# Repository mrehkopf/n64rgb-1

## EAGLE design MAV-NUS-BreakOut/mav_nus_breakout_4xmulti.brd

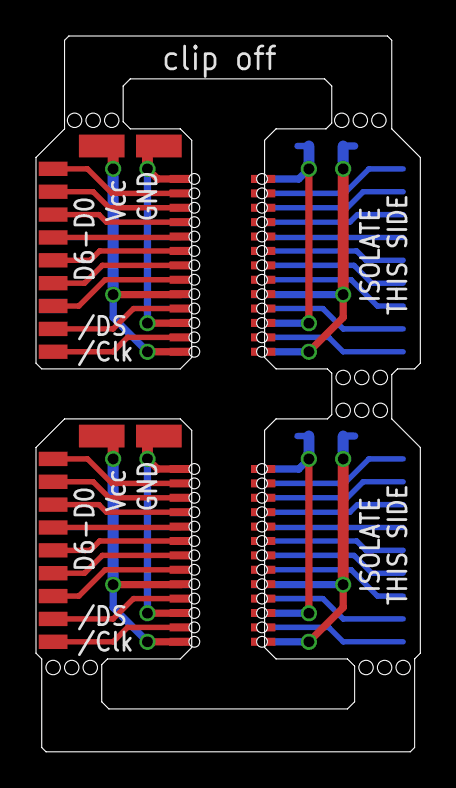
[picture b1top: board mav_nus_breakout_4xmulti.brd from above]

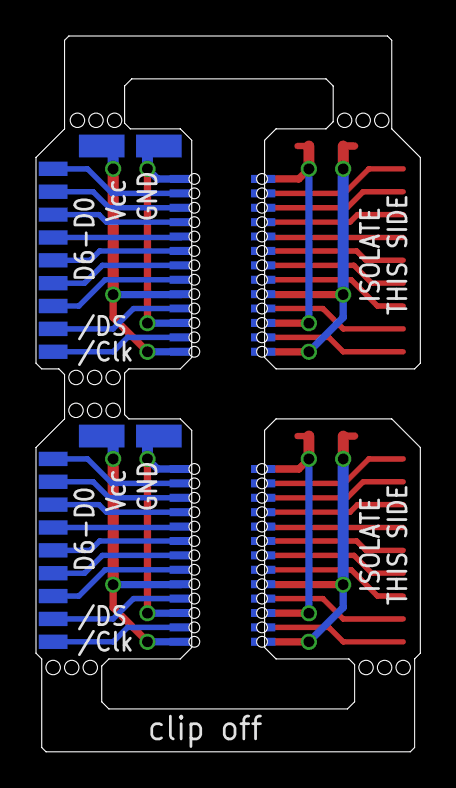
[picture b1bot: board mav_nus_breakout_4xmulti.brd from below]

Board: 2 copper layers, 21.4 x 39.8 mm, 148 parts (74 on the bottom side), 44 nets.

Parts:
PAD1, PAD2, PAD3, PAD4, PAD5, PAD6, PAD7, PAD8: SMD1,27-2,54
U$1, U$2, U$3, U$4, U$5, U$6, U$7, U$8, U$9, U$10, U$11, U$12, U$13, U$23, U$24, U$25, U$26, U$27, U$28, U$29, U$30, U$31, U$32, U$33, U$34, U$35, U$36, U$37, U$38, U$39, U$40, U$47, U$51, U$52, U$53, U$54, U$55, U$56, U$57, U$58, U$59, U$60, U$61, U$62, U$63, U$64, U$65, U$66, U$67, U$68, U$69, U$70, U$71, U$72, U$73, U$74, U$75, U$82, U$86, U$87, U$88, U$89, U$90, U$91, U$92, U$93, U$94, U$95, U$96, U$97, U$98, U$99, U$100, U$101, U$102, U$103, U$104, U$105, U$106, U$107, U$108, U$109, U$110, U$117, U$121, U$122, U$123, U$124, U$125, U$126, U$127, U$128, U$129, U$130, U$131, U$132, U$133, U$134, U$135, U$136, U$137, U$138, U$139, U$140: SMD0,45; SMD0,45-1,35
U$14, U$15, U$16, U$17, U$18, U$19, U$20, U$21, U$22, U$41, U$42, U$43, U$44, U$45, U$46, U$48, U$49, U$50, U$76, U$77, U$78, U$79, U$80, U$81, U$83, U$84, U$85, U$111, U$112, U$113, U$114, U$115, U$116, U$118, U$119, U$120: SMD1; SMD0,8-1,6

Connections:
unnamed: U$1.P$1, U$14.P$1
unnamed: U$2.P$1, U$15.P$1
unnamed: U$3.P$1, U$16.P$1
unnamed: U$4.P$1, U$17.P$1
unnamed: U$5.P$1, U$18.P$1
unnamed: U$6.P$1, U$19.P$1
unnamed: U$7.P$1, U$20.P$1
unnamed: U$8.P$1, U$21.P$1
unnamed: U$9.P$1, U$22.P$1
unnamed: PAD1.1, U$10.P$1, U$11.P$1
unnamed: PAD2.1, U$12.P$1, U$13.P$1
unnamed: U$36.P$1, U$41.P$1
unnamed: U$42.P$1, U$47.P$1
unnamed: U$43.P$1, U$51.P$1
unnamed: U$44.P$1, U$52.P$1
unnamed: U$45.P$1, U$53.P$1
unnamed: U$46.P$1, U$54.P$1
unnamed: U$48.P$1, U$55.P$1
unnamed: U$49.P$1, U$56.P$1
unnamed: U$50.P$1, U$57.P$1
unnamed: PAD3.1, U$37.P$1, U$38.P$1
unnamed: PAD4.1, U$39.P$1, U$40.P$1
unnamed: U$71.P$1, U$76.P$1
unnamed: U$77.P$1, U$82.P$1
unnamed: U$78.P$1, U$86.P$1
unnamed: U$79.P$1, U$87.P$1
unnamed: U$80.P$1, U$88.P$1
unnamed: U$81.P$1, U$89.P$1
unnamed: U$83.P$1, U$90.P$1
unnamed: U$84.P$1, U$91.P$1
unnamed: U$85.P$1, U$92.P$1
unnamed: PAD5.1, U$72.P$1, U$73.P$1
unnamed: PAD6.1, U$74.P$1, U$75.P$1
unnamed: U$106.P$1, U$111.P$1
unnamed: U$112.P$1, U$117.P$1
unnamed: U$113.P$1, U$121.P$1
unnamed: U$114.P$1, U$122.P$1
unnamed: U$115.P$1, U$123.P$1
unnamed: U$116.P$1, U$124.P$1
unnamed: U$118.P$1, U$125.P$1
unnamed: U$119.P$1, U$126.P$1
unnamed: U$120.P$1, U$127.P$1
unnamed: PAD7.1, U$107.P$1, U$108.P$1
unnamed: PAD8.1, U$109.P$1, U$110.P$1

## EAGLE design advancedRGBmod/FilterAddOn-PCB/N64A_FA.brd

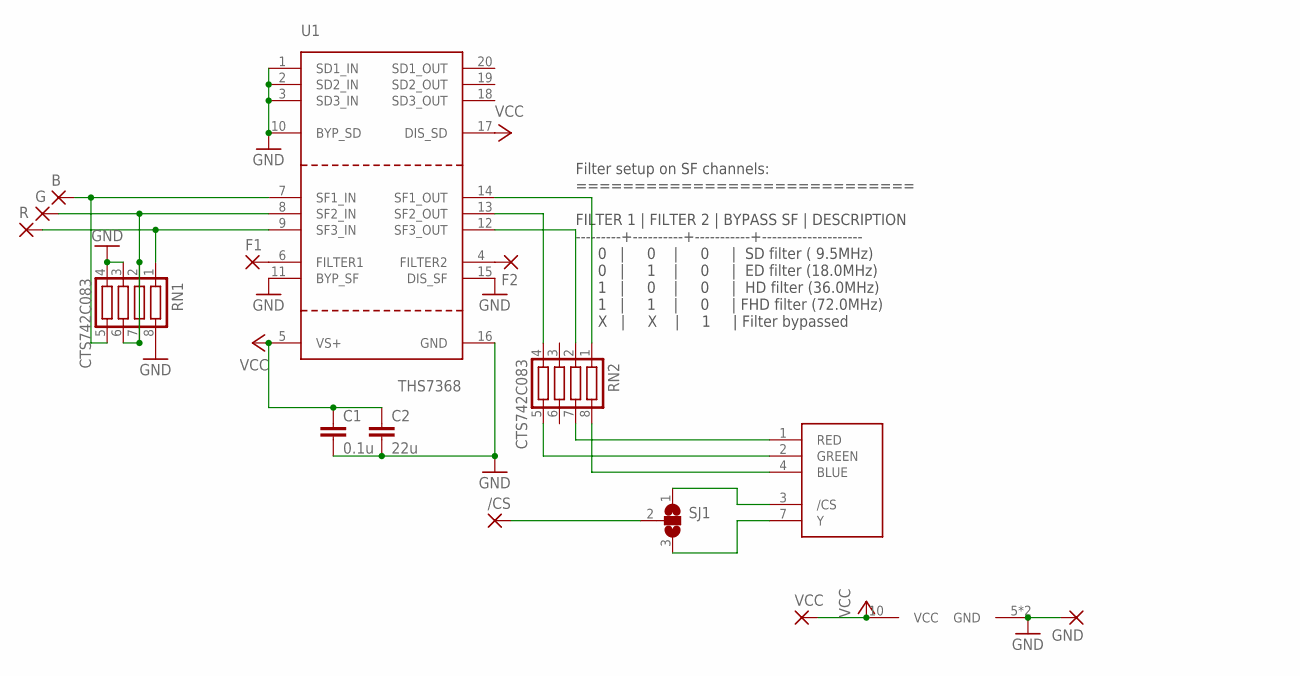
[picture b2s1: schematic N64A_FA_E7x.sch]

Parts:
/CS: SMD2; SMD1,27-2,54
B: SMD2; SMD1,27-2,54
C1: 0.1u; C0603
C2: 22u; C1206
F1, F2: SMD1; SMD0,8-1,6
G: SMD2; SMD1,27-2,54
GND: SMD2; SMD1,27-2,54
R: SMD2; SMD1,27-2,54
RN1, RN2: CTS742C083
SJ1: SJ2W; SJ_2
U1: THS7368
U$1: SNES_MULTIAV_RGBSY
VCC: SMD2; SMD1,27-2,54

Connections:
GND: C1.2, C2.2, GND.1, RN1.3, RN1.4, RN1.8, U1.1 (SD1_IN), U1.2 (SD2_IN), U1.3 (SD3_IN), U1.10 (BYP_SD), U1.11 (BYP_SF), U1.15 (DIS_SF), U1.16 (GND), U$1.5 (GND), U$1.6 (GND)
unnamed: RN2.7, U$1.1 (RED)
unnamed: RN2.8, U$1.4 (BLUE)
unnamed: RN2.5, U$1.2 (GREEN)
unnamed: RN2.4, U1.13 (SF2_OUT)
unnamed: RN2.1, U1.14 (SF1_OUT)
unnamed: RN2.2, U1.12 (SF3_OUT)
unnamed: SJ1.1, U$1.3 (/CS)
unnamed: F1.P$1, U1.6 (FILTER1)
unnamed: R.1, RN1.1, U1.9 (SF3_IN)
unnamed: G.1, RN1.2, RN1.6, RN1.7, U1.8 (SF2_IN)
unnamed: F2.P$1, U1.4 (FILTER2)
unnamed: /CS.1, SJ1.2
unnamed: B.1, RN1.5, U1.7 (SF1_IN)
unnamed: SJ1.3, U$1.7 (Y)
VCC: C1.1, C2.1, U1.5 (VS+), U1.17 (DIS_SD), U$1.10 (VCC), VCC.1

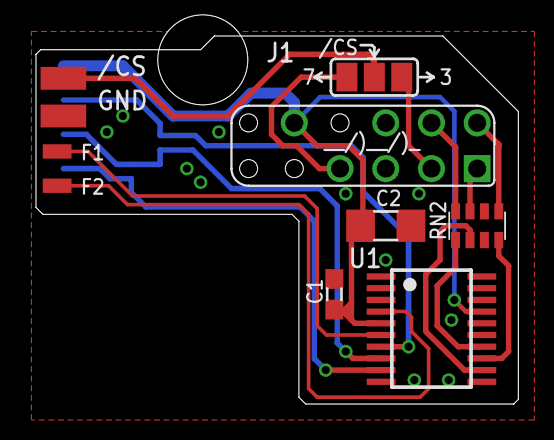
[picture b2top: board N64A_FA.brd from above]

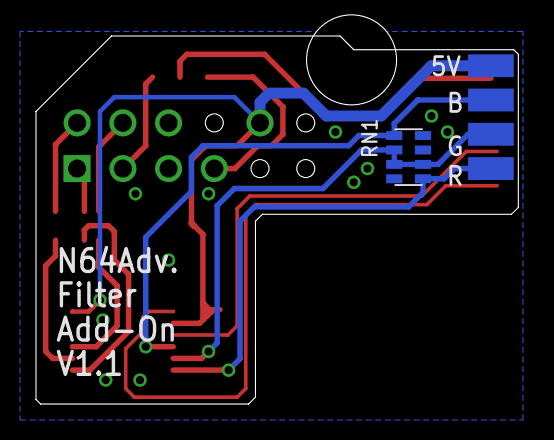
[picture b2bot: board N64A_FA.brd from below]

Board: 2 copper layers, 26.8 x 20.4 mm, 15 parts (5 on the bottom side), 16 nets.
